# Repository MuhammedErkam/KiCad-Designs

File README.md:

# KiCad-Designs
My KiCad PCB Designs

This PCB is 4 layer PCB.
Signal - GND - POWER - Signal

##### MCU - STM32F103C8T6
##### RF Module - Ai Thinker Lora Ra-02 (SX1278)
##### IMU Sensor - MPU6050
##### TEMP-PRESS Sesnor - BMP280

##### This system works with USB Micro-B
Also Micro-B connector stands for USART with CH340E

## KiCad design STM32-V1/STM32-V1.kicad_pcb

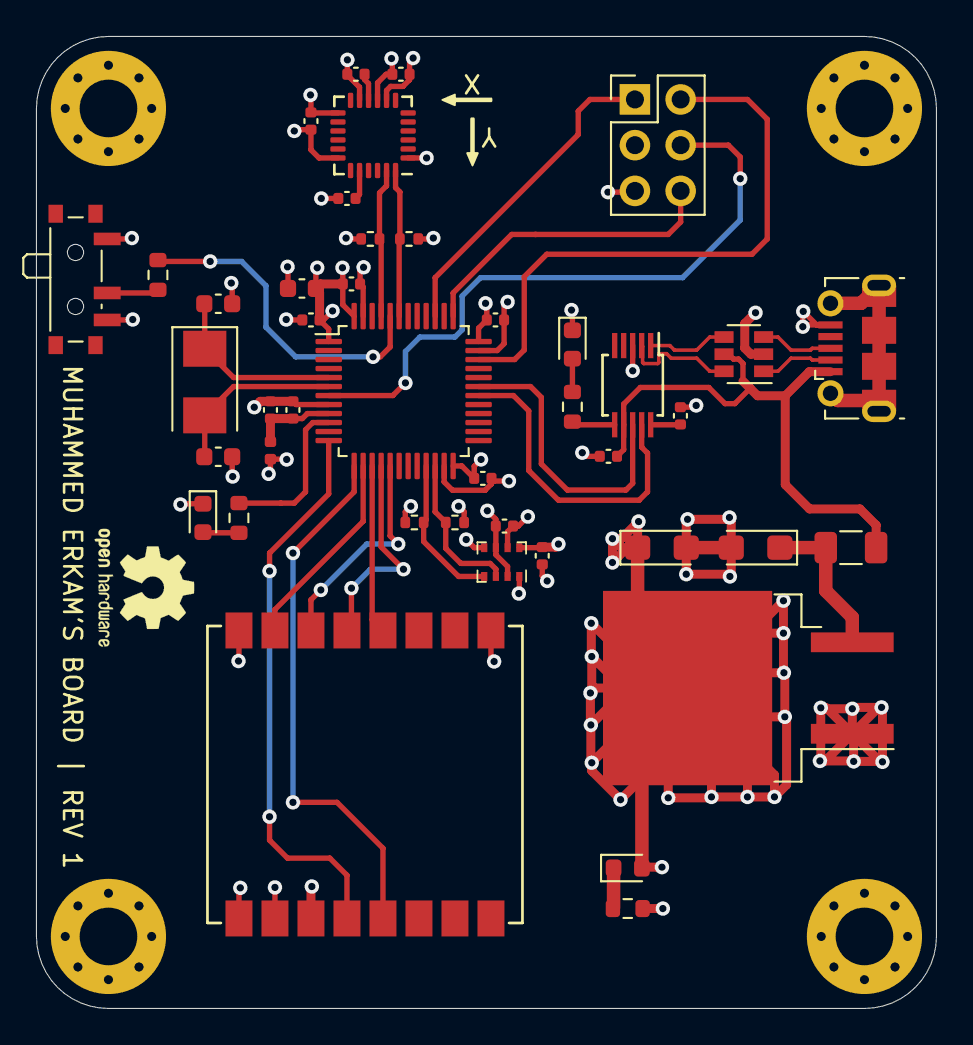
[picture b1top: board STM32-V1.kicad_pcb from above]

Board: 4 copper layers, 50.0 x 54.0 mm, 47 parts (0 on the bottom side), 37 nets.

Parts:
C1, C2: 10u; CP_EIA-3216-18_Kemet-A
C3: 4u7; C_0603_1608Metric
C4, C5, C6, C7, C11, C12, C13, C14, C18, C19: 100n; C_0402_1005Metric
C8: 1u; C_0402_1005Metric
C9: 10u; C_0402_1005Metric
C10: 10n; C_0402_1005Metric
C15: 2n2; C_0402_1005Metric
C16, C17: 30p; C_0603_1608Metric
D1, D3: RED; LED_0603_1608Metric
D2: BLUE; LED_0603_1608Metric
F1: JK-nSMD150-SF; Fuse_1206_3216Metric
H1, H2, H3, H4: MountingHole_Pad; MountingHole_3.2mm_M3_Pad_Via
J1: USB_B_Micro; USB_Micro-B_Molex-105017-0001
J2: Conn_02x03_Odd_Even; PinHeader_2x03_P2.54mm_Vertical
L1: 27n; L_0402_1005Metric
R1, R6: 1k; R_0603_1608Metric
R2: 10k; R_0603_1608Metric
R3: 1.5k; R_0603_1608Metric
R4, R5, R7, R8: 2k2; R_0402_1005Metric
SW1: SW_SPDT; SW_SPDT_PCM12
U1: LD1086D2T33TR; TO-263-2
U2: USBLC6-2SC6; SOT-23-6
U3: BMP280; Bosch_LGA-8_2x2.5mm_P0.65mm_ClockwisePinNumbering
U4: Ai-Thinker-Ra-02; Ai-Thinker-Ra-02-LoRa
U5: MPU-6050; InvenSense_QFN-24_4x4mm_P0.5mm
U6: STM32F103C8Tx; LQFP-48_7x7mm_P0.5mm
U7: CH340E; MSOP-10_3x3mm_P0.5mm
Y1: Crystal; Crystal_SMD_5032-2Pin_5.0x3.2mm

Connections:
+3.3VA: C8.1, C9.1, L1.2, U6.9
+3V3: C2.1, C3.1, C4.1, C5.1, C6.1, C7.1, C10.1, C11.1, C12.1, C13.1, D1.2, L1.1, R4.1, R5.1, R7.1, R8.1, SW1.1, U1.2, U3.2, U3.6, U3.8, U4.3, U5.8, U5.13, U6.1, U6.24, U6.36, U6.48
+5V: C18.1, F1.2, J1.1, U2.5, U7.7
BOOT0: R2.2, U6.44
DIO0_LORA: U4.5, U6.13
GND: C1.2, C2.2, C3.2, C4.2, C5.2, C6.2, C7.2, C8.2, C9.2, C10.2, C11.2, C12.2, C13.2, C14.2, C15.2, C16.2, C17.2, C18.2, C19.2, D2.1, D3.1, H1.1, H2.1, H3.1, H4.1, J1.5, J2.5, R1.2, SW1.3, U1.1, U2.2, U3.1, U3.5, U3.7, U4.1, U4.2, U4.9, U4.16, U5.1, U5.9, U5.11, U5.18, U6.8, U6.23, U6.35, U6.47, U7.3
I2C1_SCL: R5.2, U5.23, U6.45
I2C1_SDA: R4.2, U5.24, U6.43
I2C2_SCL: R7.2, U3.4, U6.21
I2C2_SDA: R8.2, U3.3, U6.22
LED_STATUS: R3.1, U6.10
LORA_NSS_SPI: U4.15, U6.14
NRESET_LORA: U4.4, U6.12
NRST: J2.4, U6.7
unnamed: C1.1, F1.1, U1.3
unnamed: C14.1, U5.10
unnamed: C15.1, U5.20
unnamed: C16.1, U6.5, Y1.1
unnamed: C17.1, U6.6, Y1.2
unnamed: C19.1, U7.10
unnamed: D1.1, R1.1
unnamed: D2.2, R3.2
unnamed: D3.2, R6.2
unnamed: R2.1, SW1.2
unnamed: R6.1, U7.6
SP1_MISO: U4.13, U6.16
SP1_SCK: U4.12, U6.15
SPI1_MOSI: U4.14, U6.17
SWCLK: J2.6, U6.37
SWDIO: J2.2, U6.34
SWO: J2.1, U6.39
USART1_RX: U6.31, U7.8
USART1_TX: U6.30, U7.9
USB_CONN_D+: J1.3, U2.3
USB_CONN_D-: J1.2, U2.1
USB_D+: U2.4, U7.1
USB_D-: U2.6, U7.2

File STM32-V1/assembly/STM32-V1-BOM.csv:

Comment,Designator,Footprint,LCSC
"10n","C10","Capacitor_SMD:C_0402_1005Metric",""
"2n2","C15","Capacitor_SMD:C_0402_1005Metric",""
"30p","C16,C17","Capacitor_SMD:C_0603_1608Metric",""
"10u","C1,C2","Capacitor_Tantalum_SMD:CP_EIA-3216-18_Kemet-A",""
"4u7","C3","Capacitor_SMD:C_0603_1608Metric",""
"100n","C4,C5,C6,C7,C11,C12,C13,C14,C18,C19","Capacitor_SMD:C_0402_1005Metric",""
"1u","C8","Capacitor_SMD:C_0402_1005Metric",""
"10u","C9","Capacitor_SMD:C_0402_1005Metric",""
"RED","D1,D3","LED_SMD:LED_0603_1608Metric",""
"BLUE","D2","LED_SMD:LED_0603_1608Metric",""
"JK-nSMD150-SF","F1","Fuse:Fuse_1206_3216Metric",""
"MountingHole_Pad","H1,H2,H3,H4","MountingHole:MountingHole_3.2mm_M3_Pad_Via",""
"USB_B_Micro","J1","Connector_USB:USB_Micro-B_Molex-105017-0001",""
"Conn_02x03_Odd_Even","J2","Connector_PinHeader_2.54mm:PinHeader_2x03_P2.54mm_Vertical",""
"27n","L1","Inductor_SMD:L_0402_1005Metric",""
"10k","R2","Resistor_SMD:R_0603_1608Metric",""
"1.5k","R3","Resistor_SMD:R_0603_1608Metric",""
"2k2","R4,R5,R7,R8","Resistor_SMD:R_0402_1005Metric",""
"1k","R1,R6","Resistor_SMD:R_0603_1608Metric",""
"SW_SPDT","SW1","Button_Switch_SMD:SW_SPDT_PCM12",""
"LD1086D2T33TR","U1","Package_TO_SOT_SMD:TO-263-2",""
"USBLC6-2SC6","U2","Package_TO_SOT_SMD:SOT-23-6",""
"BMP280","U3","Package_LGA:Bosch_LGA-8_2x2.5mm_P0.65mm_ClockwisePinNumbering",""
"Ai-Thinker-Ra-02","U4","RF_Module:Ai-Thinker-Ra-02-LoRa",""
"MPU-6050","U5","Sensor_Motion:InvenSense_QFN-24_4x4mm_P0.5mm",""
"STM32F103C8Tx","U6","Package_QFP:LQFP-48_7x7mm_P0.5mm",""
"CH340E","U7","Package_SO:MSOP-10_3x3mm_P0.5mm",""
"Crystal","Y1","Crystal:Crystal_SMD_5032-2Pin_5.0x3.2mm",""

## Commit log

2021-09-16 BOM file is missing, I will add
2021-09-16 My first KiCad Design, This is Rev 1
2021-09-27 PCB Photo is changed
